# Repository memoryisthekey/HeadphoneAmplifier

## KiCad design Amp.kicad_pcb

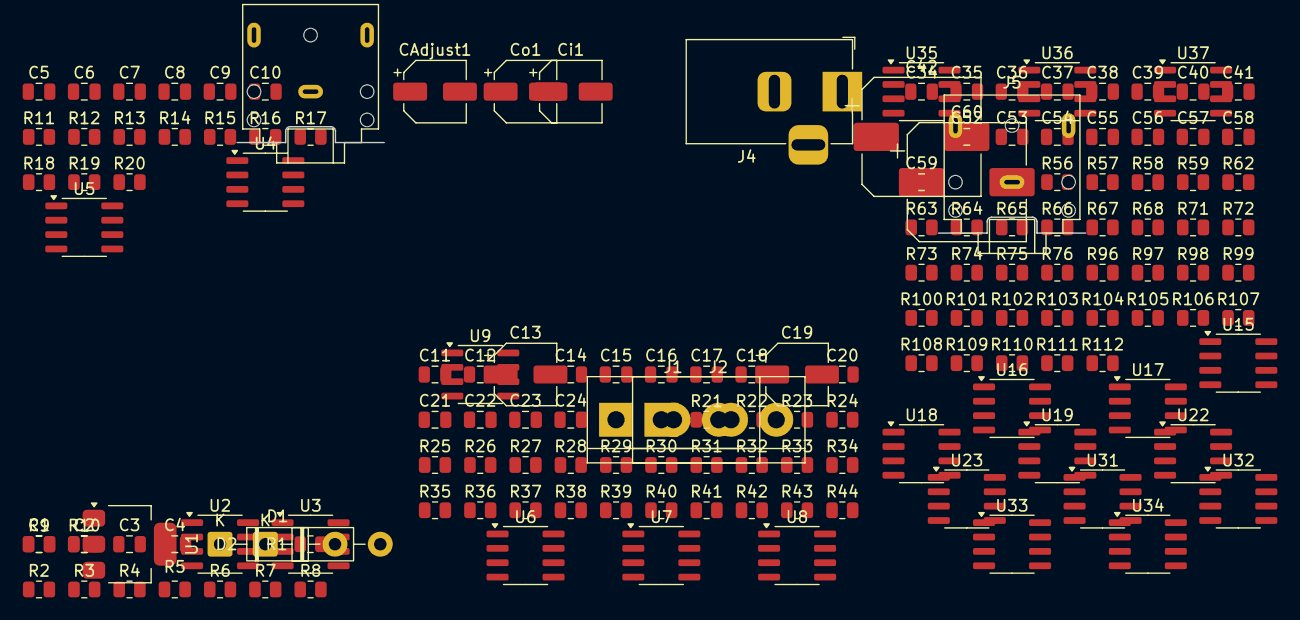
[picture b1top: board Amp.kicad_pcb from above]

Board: 2 copper layers, 153 parts (0 on the bottom side), 76 nets, no tracks yet.

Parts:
C1, C4, C14, C21, C37, C53: 10u; C_0805_2012Metric
C2, C3, C5, C10, C11, C12, C18, C20, C34, C35, C36, C38, C39, C40, C41, C52, C54, C55, C56, C57, C58, C59: 100n; C_0805_2012Metric
C6, C8: 1n; C_0805_2012Metric
C7, C9: 4.7u; C_0805_2012Metric
C13, C19: 220u; CP_Elec_5x5.3
C15, C16, C22, C23: 100p; C_0805_2012Metric
C17, C24: 470p; C_0805_2012Metric
C42, C60: 2200u; CP_Elec_10x10
CAdjust1: 10u; CP_Elec_5x5.3
Ci1: 0.1u; CP_Elec_5x5.3
Co1: 0.1u; CP_Elec_5x5.3
D1, D2: 1N4002; D_DO-41_SOD81_P10.16mm_Horizontal
J1, J2: Conn_01x03; TerminalBlock_bornier-3_P5.08mm
J3, J5: AudioJack3; Jack_3.5mm_CUI_SJ1-3523N_Horizontal
J4: Barrel_Jack; BarrelJack_Horizontal
R1: 240; R_0805_2012Metric
R2: 2.7k; R_0805_2012Metric
R3, R4, R7, R8: 2.2k; R_0805_2012Metric
R5, R6, R9, R10, R14, R15, R19, R20, R27, R29, R40, R41, R67, R68, R73, R97, R98, R111: 10; R_0805_2012Metric
R11, R16: 100; R_0805_2012Metric
R12, R13, R17, R18: 22k; R_0805_2012Metric
R21, R33: 47k; R_0805_2012Metric
R22, R23, R24, R25, R31, R34, R35, R36, R37, R43: 1k; R_0805_2012Metric
R26, R28, R38, R39: 5k6; R_0805_2012Metric
R30, R32, R42, R44: 3k3; R_0805_2012Metric
R56, R57, R58, R59, R63, R64, R65, R66, R71, R72, R75, R76, R99, R100, R101, R102, R103, R104, R105, R106, R107, R108, R109, R110: 1; R_0805_2012Metric
R62, R74, R96, R112: 10k; R_0805_2012Metric
U1: LM317_SOT-223; SOT-223-3_TabPin2
U2, U3, U4, U5, U6, U7, U8, U9, U15, U16, U17, U18, U19, U22, U23, U31, U32, U33, U34, U35, U36, U37: NE5532; SOIC-8_3.9x4.9mm_P1.27mm

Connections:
+15V: C2.1, C3.1, C4.1, C5.1, C10.1, C11.1, C12.1, C18.1, C20.1, C34.1, C35.1, C36.1, C38.1, C39.1, C40.1, C41.1, C52.1, C54.1, C55.1, C56.1, C57.1, C58.1, C59.1, Co1.1, D1.2 (A), D2.1 (K), R1.1, R3.1, R7.1, U1.2 (VO), U2.8 (V+), U3.8 (V+), U4.8 (V+), U5.8 (V+), U6.8 (V+), U7.8 (V+), U8.8 (V+), U9.8 (V+), U15.8 (V+), U16.8 (V+), U17.8 (V+), U18.8 (V+), U19.8 (V+), U22.8 (V+), U23.8 (V+), U31.8 (V+), U32.8 (V+), U33.8 (V+), U34.8 (V+), U35.8 (V+), U36.8 (V+), U37.8 (V+)
BUF_IN_LEFT: R98.1, U32.3 (+), U32.5 (+), U33.3 (+), U33.5 (+), U34.3 (+), U34.5 (+), U35.3 (+), U35.5 (+), U36.3 (+), U36.5 (+), U37.3 (+), U37.5 (+)
BUF_IN_RIGHT: R68.1, U15.3 (+), U15.5 (+), U16.3 (+), U16.5 (+), U18.3 (+), U18.5 (+), U19.3 (+), U19.5 (+), U22.3 (+), U22.5 (+), U23.3 (+), U23.5 (+)
BUF_OUT_LEFT: R100.1, R101.1, R102.1, R103.1, R104.1, R105.1, R106.1, R107.1, R108.1, R109.1, R110.1, R111.1
BUF_OUT_RIGHT: R57.1, R58.1, R59.1, R63.1, R64.1, R65.1, R66.1, R71.1, R72.1, R73.1, R75.1, R76.1
GND: C2.2, C3.2, C4.2, C5.2, C6.2, C8.2, C10.2, C11.2, C12.2, C18.2, C20.2, C34.2, C35.2, C36.2, C38.2, C39.2, C40.2, C41.2, C52.2, C54.2, C55.2, C56.2, C57.2, C58.2, C59.2, CAdjust1.2, Ci1.2, Co1.2, J3.S, J4.2, J5.S, R2.2, R4.2, R8.2, R12.1, R17.1, R74.1, R112.1, U2.4 (V-), U3.4 (V-), U4.4 (V-), U5.4 (V-), U6.4 (V-), U7.4 (V-), U8.4 (V-), U9.4 (V-), U15.4 (V-), U16.4 (V-), U17.4 (V-), U18.4 (V-), U19.4 (V-), U22.4 (V-), U23.4 (V-), U31.4 (V-), U32.4 (V-), U33.4 (V-), U34.4 (V-), U35.4 (V-), U36.4 (V-), U37.4 (V-)
HP_OUT_LEFT: J5.T, R112.2
HP_OUT_RIGHT: J5.R, R74.2
INP_BUF_OUT_LEFT: R14.2, R15.2
INP_BUF_OUT_RIGHT: R19.2, R20.2
unnamed: C7.1, R11.1, R12.2
unnamed: C9.1, R16.1, R17.2
unnamed: R26.1, R27.2, U6.1
unnamed: R28.1, R29.2, U7.1
unnamed: R38.1, R40.2, U9.1
unnamed: R39.1, R41.2, U8.1
unnamed: D2.2 (A), R1.2, R2.1, U1.1 (ADJ)
unnamed: R27.1, R29.1, R32.2
unnamed: R40.1, R41.1, R42.2
unnamed: R4.1, U2.3 (+), U2.5 (+)
unnamed: U2.1, U2.2 (-)
unnamed: U2.6 (-), U2.7
unnamed: R8.1, U3.3 (+), U3.5 (+)
unnamed: U3.1, U3.2 (-)
unnamed: U3.6 (-), U3.7
unnamed: R13.2, U4.3 (+), U4.5 (+)
unnamed: U4.1, U4.2 (-)
unnamed: U4.6 (-), U4.7
unnamed: R18.2, U5.3 (+), U5.5 (+)
unnamed: U5.1, U5.2 (-)
unnamed: U5.6 (-), U5.7
unnamed: R22.2, R26.2, U6.3 (+)
unnamed: R21.2, U6.5 (+)
unnamed: R25.1, U6.6 (-), U6.7
unnamed: R25.2, R28.2, U7.3 (+)
unnamed: R30.2, R32.1, U7.6 (-)
unnamed: R37.2, R39.2, U8.3 (+)
unnamed: R42.1, R44.2, U8.6 (-)
unnamed: R36.2, R38.2, U9.3 (+)
unnamed: R33.2, U9.5 (+)
unnamed: R37.1, U9.6 (-), U9.7
unnamed: U15.1, U15.2 (-)
unnamed: U15.6 (-), U15.7
unnamed: U16.1, U16.2 (-)
unnamed: U16.6 (-), U16.7
unnamed: R62.1, U17.3 (+), U17.5 (+)
unnamed: U17.1, U17.2 (-)
unnamed: U17.6 (-), U17.7
unnamed: U18.1, U18.2 (-)
unnamed: U18.6 (-), U18.7
unnamed: U19.1, U19.2 (-)
unnamed: U19.6 (-), U19.7
unnamed: U22.1, U22.2 (-)
unnamed: U22.6 (-), U22.7
unnamed: U23.1, U23.2 (-)
unnamed: U23.6 (-), U23.7
unnamed: R96.1, U31.3 (+), U31.5 (+)
unnamed: U31.1, U31.2 (-)
unnamed: U31.6 (-), U31.7
unnamed: U32.1, U32.2 (-)
unnamed: U32.6 (-), U32.7
unnamed: U33.1, U33.2 (-)
unnamed: U33.6 (-), U33.7
unnamed: U34.1, U34.2 (-)
unnamed: U34.6 (-), U34.7
unnamed: U35.1, U35.2 (-)
unnamed: U35.6 (-), U35.7
unnamed: U36.1, U36.2 (-)
unnamed: U36.6 (-), U36.7
unnamed: U37.1, U37.2 (-)
unnamed: U37.6 (-), U37.7
VAS_OUT_LEFT: C53.1, R30.1, U7.7
VAS_OUT_RIGHT: C37.1, R44.1, U8.7
VBIAS_LEFT: R6.2, R13.1, R21.1, R23.2, R24.2, R31.2, R96.2
VBIAS_RIGHT: R10.2, R18.1, R33.1, R34.2, R35.2, R43.2, R62.2
Vi: D1.1 (K), J4.1, U1.3 (VI)

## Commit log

2025-09-01 Power Input: LM317 Done
2025-09-07 Finish Power Section & Make multisheet schema
2025-09-09 Finish Input Buffer & Add Volume Control Sheet
2025-09-14 Complete Volume Control
2025-09-14 Finish Output Stage & Finish Schematic
2025-09-16 Add missing C values
2025-09-18 Add Footprints
2025-09-22 Add inputs audio and power and correct errors
2025-09-25 added free routing plugin
